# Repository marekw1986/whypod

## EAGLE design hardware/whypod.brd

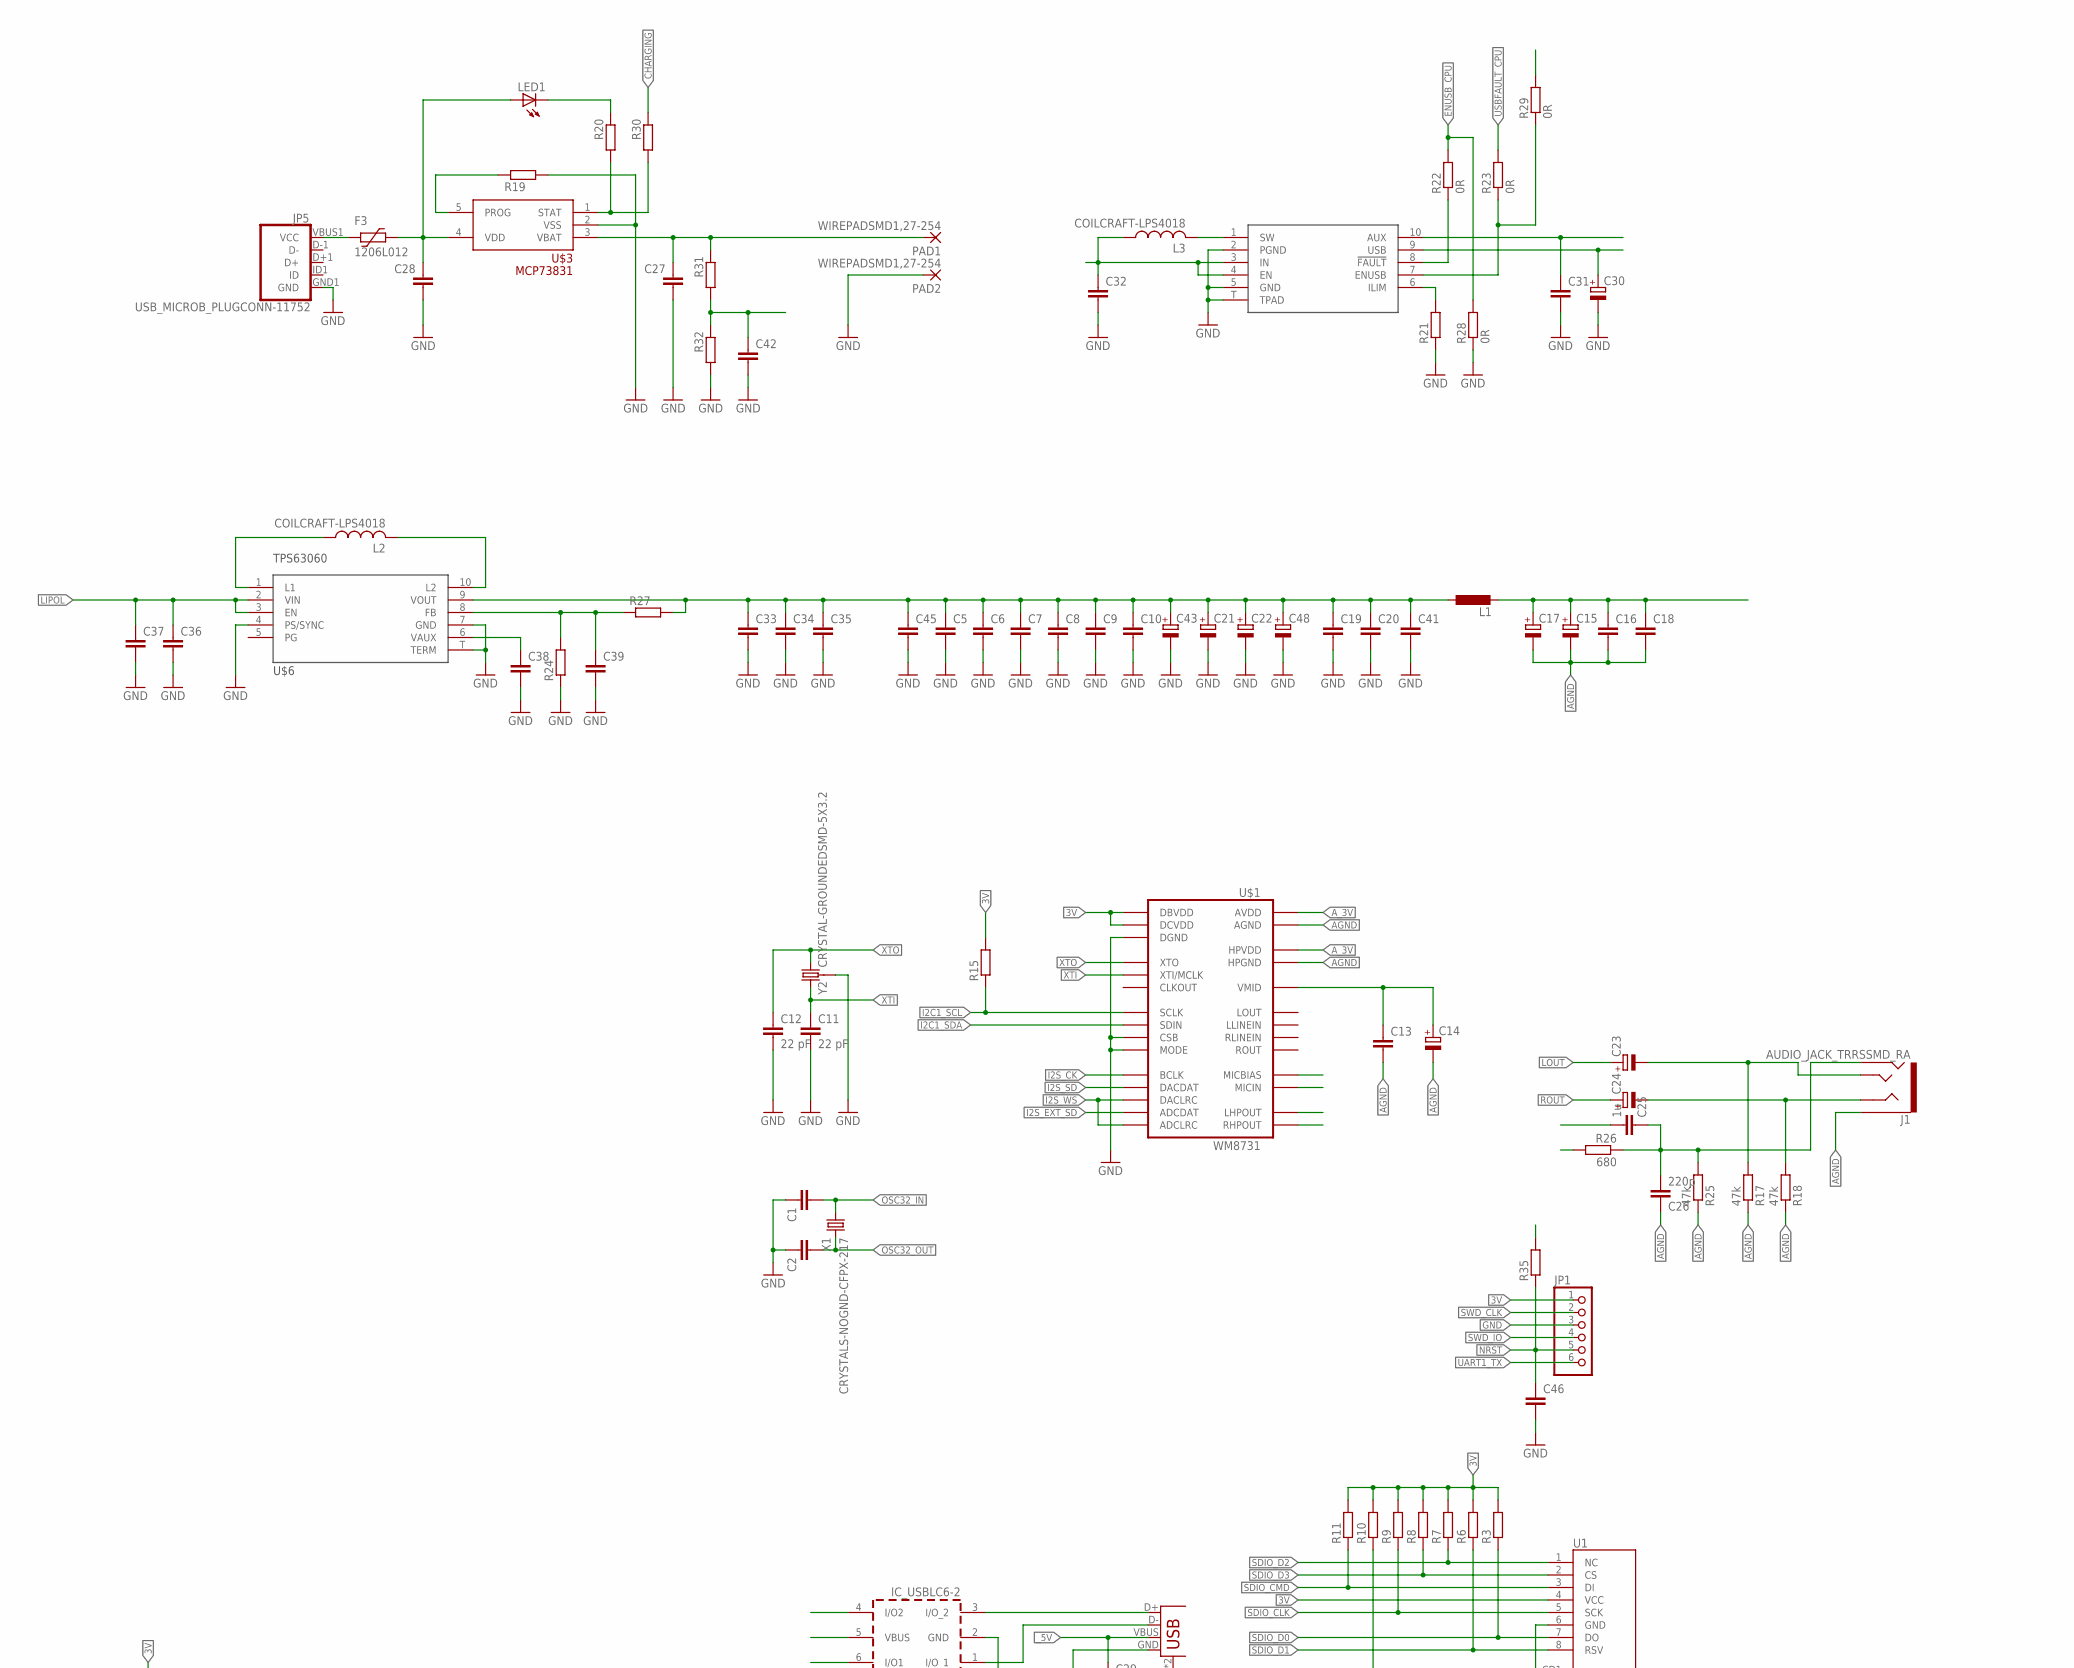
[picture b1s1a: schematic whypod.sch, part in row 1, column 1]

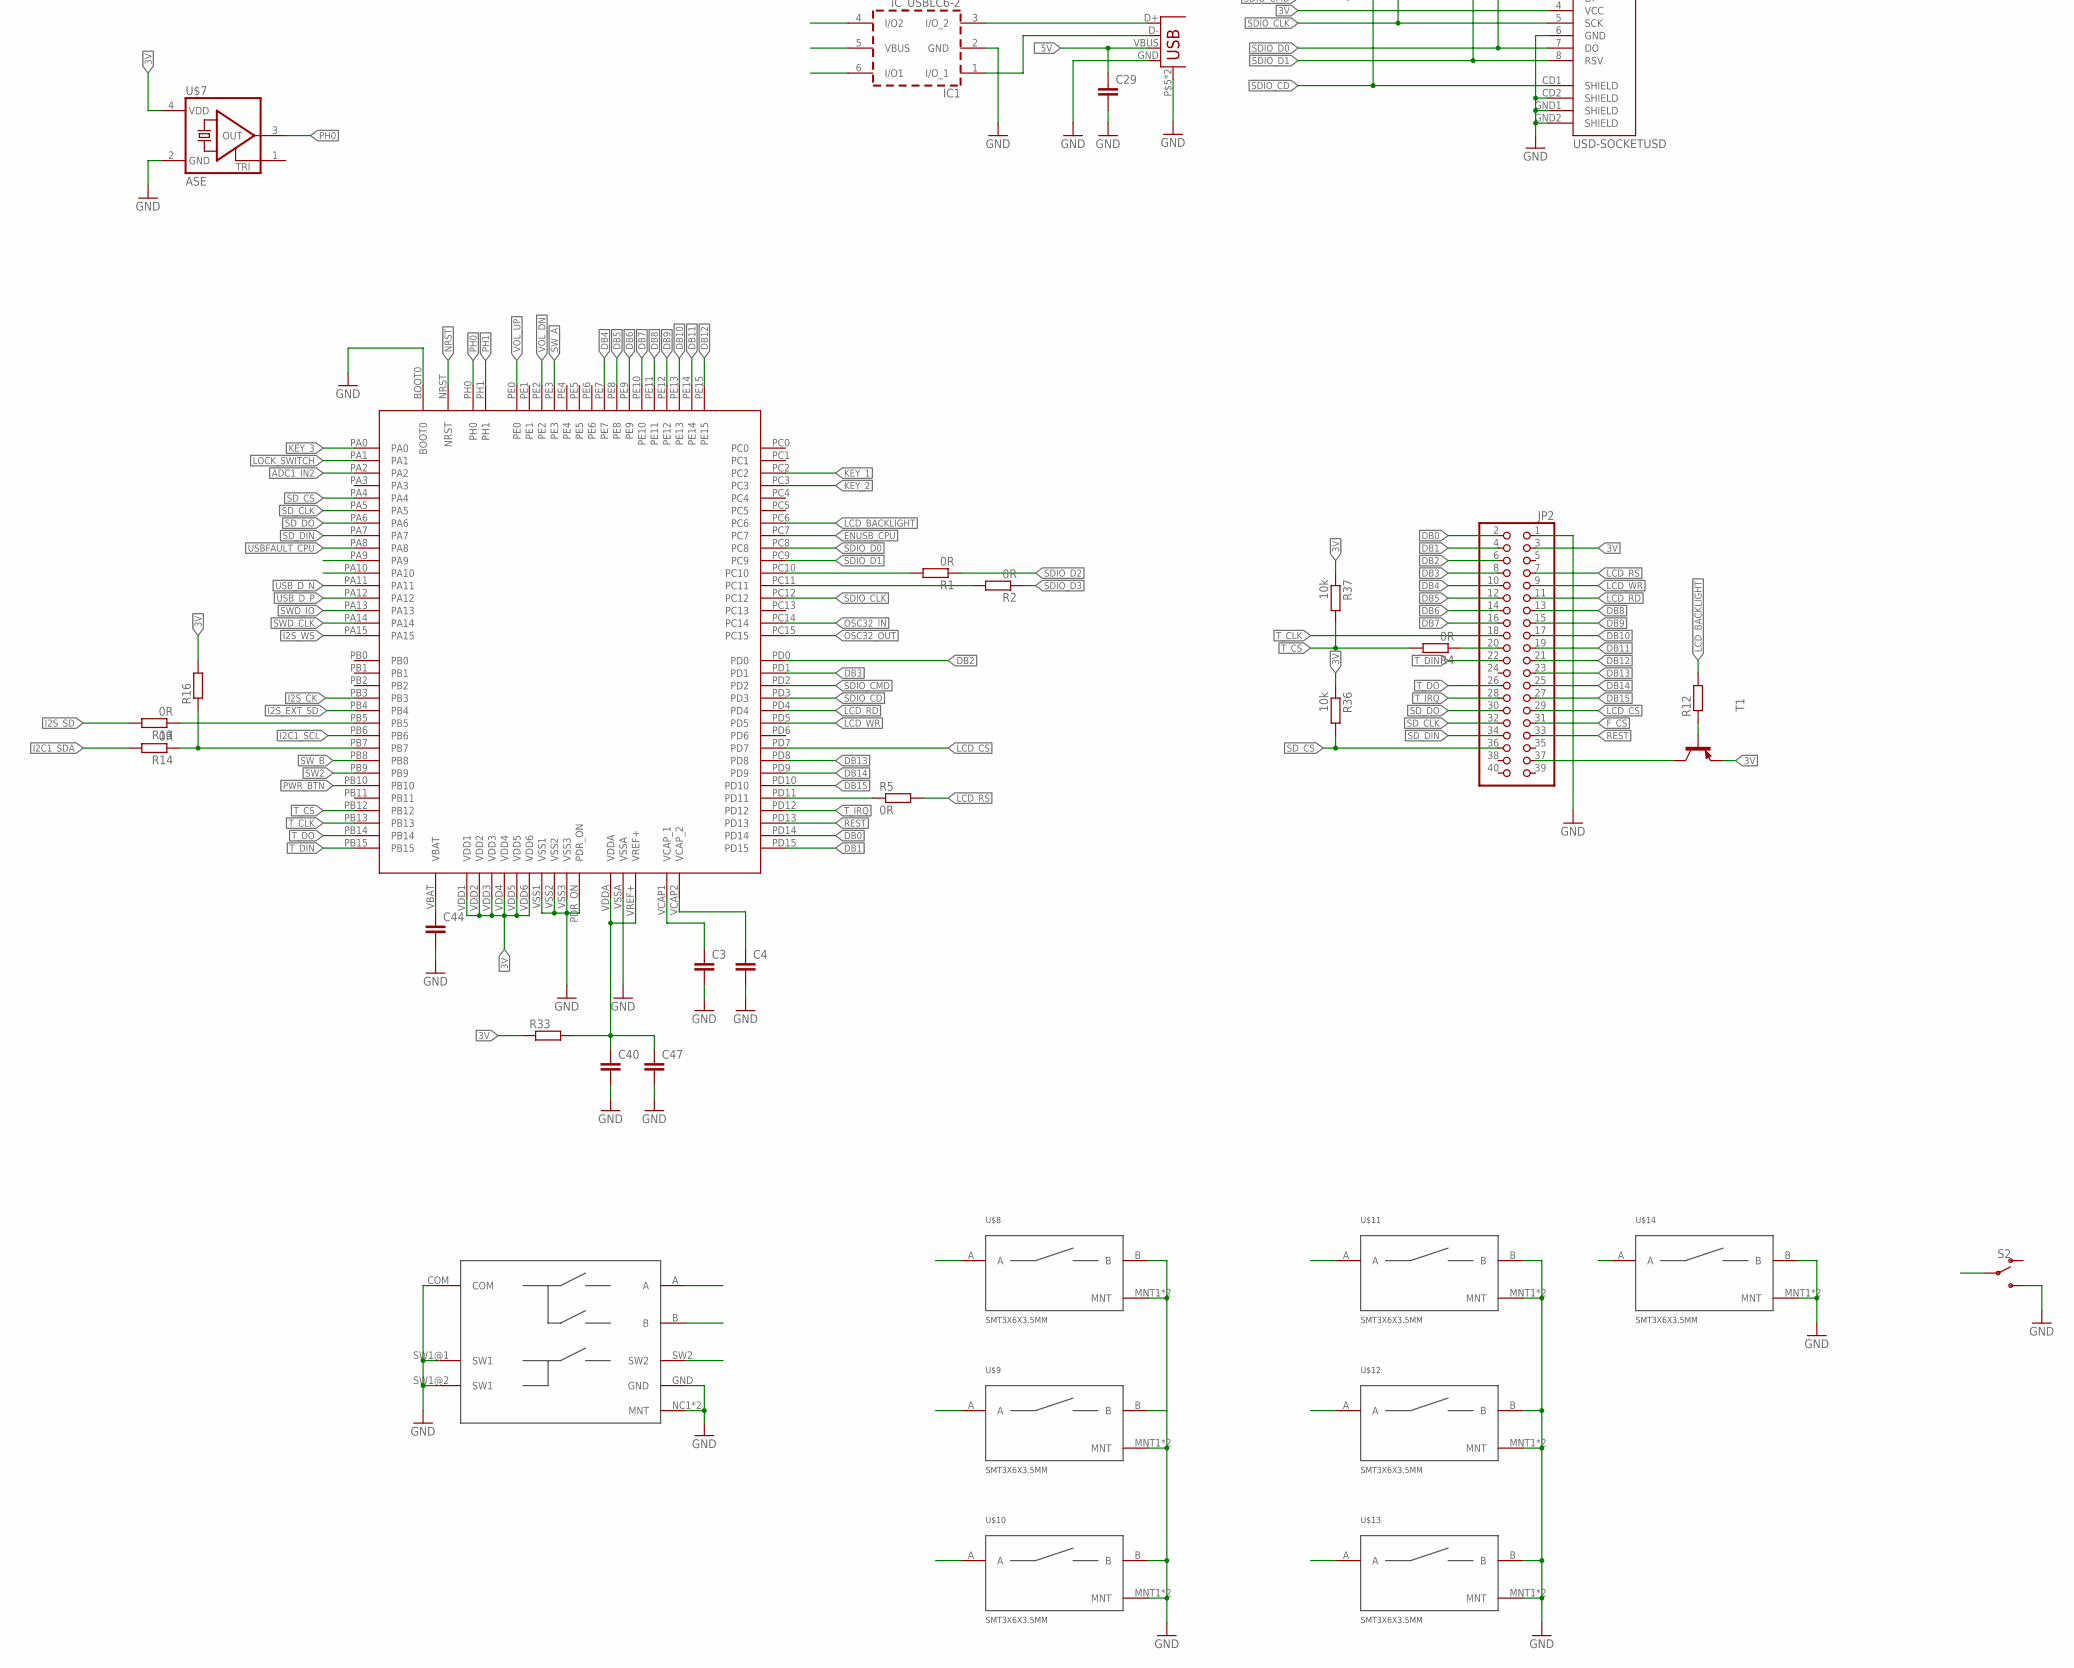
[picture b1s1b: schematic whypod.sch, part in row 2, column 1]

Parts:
C1, C2, C3, C4, C5, C6, C8, C9, C10, C13, C16, C18, C19, C20, C27, C28, C29, C31, C32, C38, C42, C46, C47: C-EUC0603; C0603
C7, C39, C40, C41, C44, C45: C-EUC0402; C0402
C11, C12: 22 pF; C0603
C14, C15, C17, C21, C22, C43, C48: CPOL-EUSMCA; SMC_A
C23, C24: CPOL-EUSMCE; SMC_E
C25: 1u; C0603
C26: 220p; C0603
C30: CPOL-EUSMCD; SMC_D
C33, C34, C35, C36, C37: C-EUC0805; C0805
F3: 1206L012; 1206L
IC1: IC_USBLC6-2; SOT-23-6L
J1: AUDIO_JACK_TRRSSMD_RA; AUDIO_JACK_3.5MM_TRRS_SMD_RA
JP1: PINHD-1X06_2.54-SMD-90°; 1X06SMD/90
JP2: PINHD-2X20_2.54-SMD; 2X20SMD
JP5: USB_MICROB_PLUGCONN-11752; USB-B-MICRO-SMD_V03
L1: L-EUL3225M; L3225M
L2, L3: COILCRAFT-LPS4018; LPS4018
LED1: LEDCHIP-LED0603; CHIP-LED0603
PAD1, PAD2: WIREPADSMD1,27-254; SMD1,27-2,54
R1, R2, R4, R5, R13, R14, R22, R23, R28, R29: 0R; R0603
R3, R6, R8, R10, R11, R15, R19, R20, R21, R30, R31, R32, R35: R-EU_R0603; R0603
R7, R9, R12, R16, R24, R27: R-EU_R0402; R0402
R17, R18, R25: 47k; R0603
R26: 680; R0603
R33: R-EU_M0805; M0805
R36, R37: 10k; R0603
S2: SWITCH-SPDT-SMD-RIGHT-ANGLE; SWITCH_SPST_SMD_A
T1: BC857A-PNP-SOT23-BEC; SOT23-BEC
U1: USD-SOCKETUSD; USD-SOCKET-PP
U$1: WM8731; 28-SSOP
U$2: STM32F4V_100PIN_GENERIC; LQFP100
U$3: MCP73831SOT-23-5; SOT-23-5
U$4: EVQWKSMD; EVQWK_SMD
U$5: TPS2500; DRC10
U$6: TPS63060; DRC10
U$7: ASE
U$8, U$9, U$10, U$11, U$12, U$13, U$14: SMT3X6X3.5MM
X1: CRYSTALS-NOGND-CFPX-217; 3.2X1.5-2-PAD
X2: USB-A-S
Y2: CRYSTAL-GROUNDEDSMD-5X3.2; CRYSTAL-SMD-5X3.2-4PAD

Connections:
3V: C5.1, C6.1, C7.1, C8.1, C9.1, C10.1, C19.1, C20.1, C21.+, C22.+, C33.1, C34.1, C35.1, C41.1, C43.+, C45.1, C48.+, JP1.1, JP2.3, L1.1, R3.2, R6.2, R7.2, R8.2, R9.2, R10.2, R11.2, R15.2, R16.2, R27.2, R29.2, R33.1, R35.2, R36.1, R37.1, T1.E, U1.4 (VCC), U$1.P$1 (DBVDD), U$1.P$27 (DCVDD), U$2.VDD1, U$2.VDD2, U$2.VDD3, U$2.VDD4, U$2.VDD5, U$2.VDD6, U$6.9 (VOUT), U$7.4 (VDD)
ADC1_IN2: C42.1, R31.2, R32.1, U$2.PA2
AGND: C13.2, C14.-, C15.-, C16.2, C17.-, C18.2, C26.1, J1.EARTH, R17.1, R18.1, R25.1, U$1.P$11 (HPGND), U$1.P$15 (AGND)
A_3V: C15.+, C16.1, C17.+, C18.1, L1.2, U$1.P$8 (HPVDD), U$1.P$14 (AVDD)
CHARGING: R30.1, U$2.PA10
DB0: JP2.2, U$2.PD14
DB1: JP2.4, U$2.PD15
DB2: JP2.6, U$2.PD0
DB3: JP2.8, U$2.PD1
DB4: JP2.10, U$2.PE7
DB5: JP2.12, U$2.PE8
DB6: JP2.14, U$2.PE9
DB7: JP2.16, U$2.PE10
DB8: JP2.13, U$2.PE11
DB9: JP2.15, U$2.PE12
DB10: JP2.17, U$2.PE13
DB11: JP2.19, U$2.PE14
DB12: JP2.21, U$2.PE15
DB13: JP2.23, U$2.PD8
DB14: JP2.25, U$2.PD9
DB15: JP2.27, U$2.PD10
ENUSB: R22.1, U$5.8 (!FAULT)
ENUSB_CPU: R22.2, R28.2, U$2.PC7
F_CS: JP2.31
GND: C1.1, C2.1, C3.2, C4.2, C5.2, C6.2, C7.2, C8.2, C9.2, C10.2, C11.2, C12.2, C19.2, C20.2, C21.-, C22.-, C27.2, C28.2, C29.2, C30.-, C31.2, C32.2, C33.2, C34.2, C35.2, C36.2, C37.2, C38.2, C39.2, C40.2, C41.2, C42.2, C43.-, C44.2, C45.2, C46.2, C47.2, C48.-, IC1.2 (GND), JP1.3, JP2.1, JP5.GND1 (GND), PAD2.1, R19.2, R21.1, R24.1, R28.1, R32.2, S2.3 (S), U1.6 (GND), U1.CD2 (SHIELD), U1.GND1 (SHIELD), U1.GND2 (SHIELD), U$1.P$21 (MODE), U$1.P$22 (CSB), U$1.P$28 (DGND), U$2.BOOT0, U$2.PDR_ON, U$2.VSS1, U$2.VSS2, U$2.VSS3, U$2.VSSA, U$3.2 (VSS), U$4.COM, U$4.GND, U$4.NC1 (MNT), U$4.NC2 (MNT), U$4.SW1@1 (SW1), U$4.SW1@2 (SW1), U$5.2 (PGND), U$5.5 (GND), U$5.T (TPAD), U$6.4 (PS/SYNC), U$6.7 (GND), U$6.T (TERM), U$7.2 (GND), U$8.B, U$8.MNT1 (MNT), U$8.MNT2 (MNT), U$9.B, U$9.MNT1 (MNT), U$9.MNT2 (MNT), U$10.B, U$10.MNT1 (MNT), U$10.MNT2 (MNT), U$11.B, U$11.MNT1 (MNT), U$11.MNT2 (MNT), U$12.B, U$12.MNT1 (MNT), U$12.MNT2 (MNT), U$13.B, U$13.MNT1 (MNT), U$13.MNT2 (MNT), U$14.B, U$14.MNT1 (MNT), U$14.MNT2 (MNT), X2.GND, X2.P$5 (SHIELD), X2.P$6 (SHIELD), Y2.2 (3), Y2.4 (3)
I2C1_SCL: R15.1, U$1.P$24 (SCLK), U$2.PB6
I2C1_SDA: R14.2, U$1.P$23 (SDIN)
I2S_CK: U$1.P$3 (BCLK), U$2.PB3
I2S_EXT_SD: U$1.P$6 (ADCDAT), U$2.PB4
I2S_SD: R13.2, U$1.P$4 (DACDAT)
I2S_WS: U$1.P$5 (DACLRC), U$1.P$7 (ADCLRC), U$2.PA15
KEY_1: U$2.PC2, U$11.A
KEY_2: U$2.PC3, U$12.A
KEY_3: U$2.PA0, U$13.A
LCD_BACKLIGHT: R12.2, U$2.PC6
LCD_CS: JP2.29, U$2.PD7
LCD_RD: JP2.11, U$2.PD4
LCD_RS: JP2.7, R5.2
LCD_WR: JP2.9, U$2.PD5
LED_A: JP2.37, T1.C
LIPOL: C27.1, C32.1, C36.1, C37.1, L3.1, PAD1.1, R31.1, U$3.3 (VBAT), U$5.3 (IN), U$5.4 (EN), U$6.2 (VIN), U$6.3 (EN)
LOCK_SWITCH: S2.2, U$2.PA1
LOUT: C23.+, U$1.P$9 (LHPOUT)
MICBIAS: R26.2, U$1.P$17 (MICBIAS)
MICIN: C25.2, U$1.P$18 (MICIN)
unnamed: IC1.3 (I/O_2), X2.D+
unnamed: IC1.1 (I/O_1), X2.D-
unnamed: JP2.20, R4.1
unnamed: R5.1, U$2.PD11
unnamed: R1.2, U$2.PC10
unnamed: C3.1, U$2.VCAP1 (VCAP_1)
unnamed: C4.1, U$2.VCAP2 (VCAP_2)
unnamed: R2.2, U$2.PC11
unnamed: R12.1, T1.B
unnamed: C13.1, C14.+, U$1.P$16 (VMID)
unnamed: C23.-, J1.TIP, R17.2
unnamed: R13.1, U$2.PB5
unnamed: C24.-, J1.RING1, R18.2
unnamed: R14.1, R16.1, U$2.PB7
unnamed: R19.1, U$3.5 (PROG)
unnamed: R20.2, R30.2, U$3.1 (STAT)
unnamed: LED1.C, R20.1
unnamed: F3.2, JP5.VBUS1 (VCC)
unnamed: R21.2, U$5.6 (ILIM)
unnamed: C31.1, U$5.10 (AUX)
unnamed: C38.1, U$6.6 (VAUX)
unnamed: L3.2, U$5.1 (SW)
unnamed: C39.1, R24.2, R27.1, U$6.8 (FB)
unnamed: L2.2, U$6.10 (L2)
unnamed: L2.1, U$6.1 (L1)
unnamed: C40.1, C47.1, R33.2, U$2.VDDA, U$2.VREF+
unnamed: C44.1, U$2.VBAT
unnamed: C25.1, C26.2, J1.RING2, R25.2, R26.1
NRST: C46.1, JP1.5, R35.1, U$2.NRST, U$14.A
OSC32_IN: C1.2, U$2.PC14, X1.1
OSC32_OUT: C2.2, U$2.PC15, X1.2
PH0: U$2.PH0, U$7.3 (OUT)
PH1: U$2.PH1
PWR_BTN: U$2.PB10, U$8.A
REST: JP2.33, U$2.PD13
ROUT: C24.+, U$1.P$10 (RHPOUT)
SDIO_CD: R10.1, U1.CD1 (SHIELD), U$2.PD3
SDIO_CLK: R9.1, U1.5 (SCK), U$2.PC12
SDIO_CMD: R11.1, U1.3 (DI), U$2.PD2
SDIO_D0: R3.1, U1.7 (DO), U$2.PC8
SDIO_D1: R6.1, U1.8 (RSV), U$2.PC9
SDIO_D2: R1.1, R7.1, U1.1 (NC)
SDIO_D3: R2.1, R8.1, U1.2 (CS)
SD_CLK: JP2.32, U$2.PA5
SD_CS: JP2.36, R36.2, U$2.PA4
SD_DIN: JP2.34, U$2.PA7
SD_DO: JP2.30, U$2.PA6
SW2: U$2.PB9, U$4.SW2
SWD_CLK: JP1.2, U$2.PA14
SWD_IO: JP1.4, U$2.PA13
SW_A: U$2.PE3, U$4.A
SW_B: U$2.PB8, U$4.B
T_CLK: JP2.18, U$2.PB13
T_CS: R4.2, R37.2, U$2.PB12
T_DIN: JP2.22, U$2.PB15
T_DO: JP2.26, U$2.PB14
T_IRQ: JP2.28, U$2.PD12
UART1_TX: JP1.6, U$2.PA9
USBFAULT: R23.1, R29.1, U$5.7 (ENUSB)
USBFAULT_CPU: R23.2, U$2.PA8
USB_D_N: IC1.6 (I/O1), U$2.PA11
USB_D_P: IC1.4 (I/O2), U$2.PA12
VBUS: C28.1, F3.1, LED1.A, U$3.4 (VDD)
VOL_DN: U$2.PE2, U$10.A
VOL_UP: U$2.PE0, U$9.A
XTI: C11.1, U$1.P$25 (XTI/MCLK), Y2.3 (1)
XTO: C12.1, U$1.P$26 (XTO), Y2.1 (2)
_5V: C29.1, C30.+, IC1.5 (VBUS), U$5.9 (USB), X2.VBUS

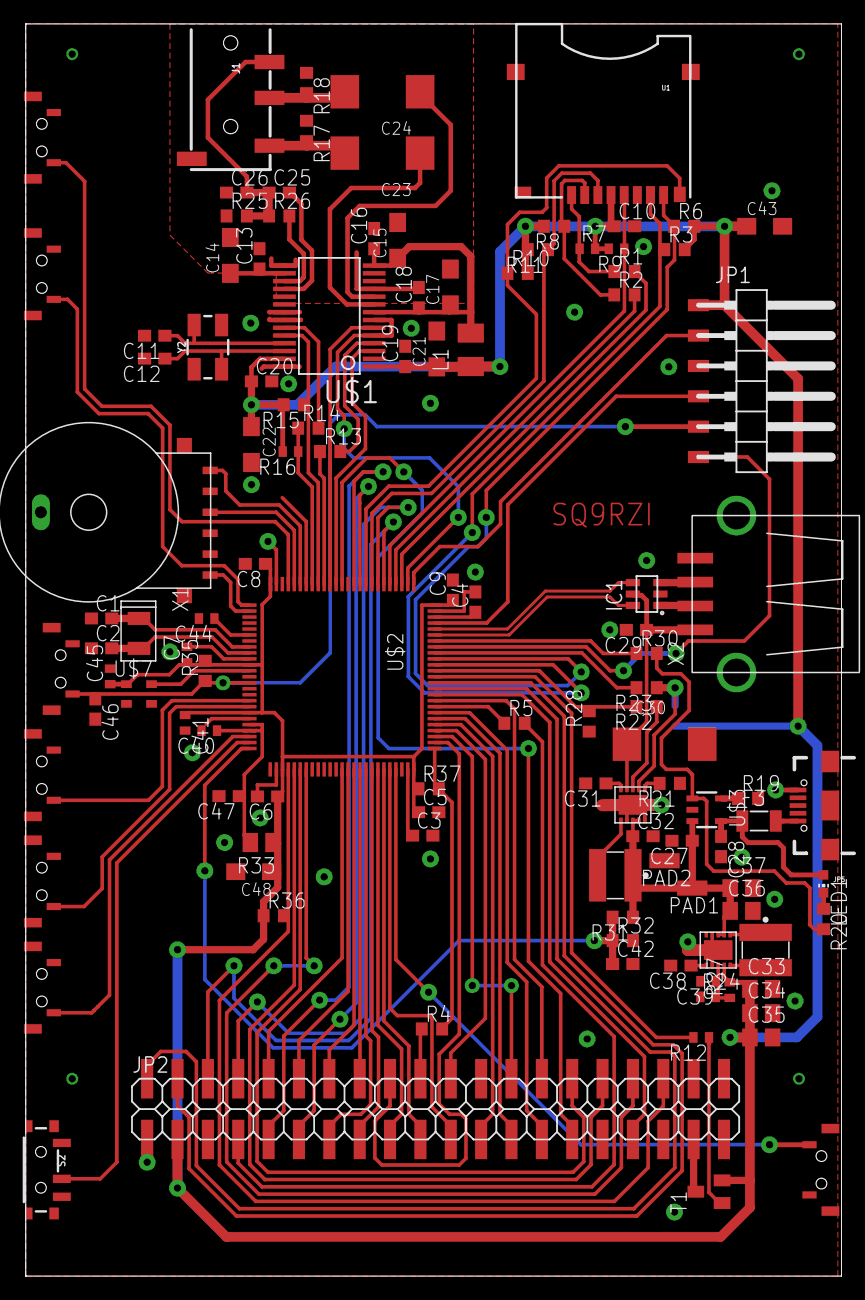
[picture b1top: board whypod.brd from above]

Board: 2 copper layers, 68.2 x 104.8 mm, 116 parts (1 on the bottom side), 111 nets.

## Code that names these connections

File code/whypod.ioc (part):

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PD7.Mode=NorPsramChipSelect1_1
PC7.GPIOParameters=GPIO_Label
PH0-OSC_IN.Signal=RCC_OSC_IN
PB10.GPIO_PuPd=GPIO_PULLUP
PA10.GPIO_PuPd=GPIO_PULLUP
PC12.Signal=SDIO_CK
PD3.GPIOParameters=GPIO_Label
PC6.GPIO_Label=LCD_BACKLIGHT
PB13.Signal=SPI2_SCK
RCC.SYSCLKSource=RCC_SYSCLKSOURCE_PLLCLK
PA9.GPIO_ModeDefaultOD=GPIO_MODE_AF_PP
PD4.Signal=FSMC_NOE
PB6.Signal=I2C1_SCL
PC7.Signal=GPIO_Output
PB6.Mode=I2C
PC3.Signal=GPIO_Input
PD0.Signal=FSMC_D2
PD8.Signal=FSMC_D13
PA1.GPIO_PuPd=GPIO_PULLUP
PB3.Mode=Full_Duplex_Master
PB12.GPIO_Label=T_IRQ
PE0.GPIOParameters=GPIO_PuPd,GPIO_Label
PA1.GPIOParameters=GPIO_PuPd,GPIO_Label
PE9.Signal=FSMC_D6
PB14.Mode=Full_Duplex_Master
PC9.Mode=SD_4_bits_Wide_bus
PE2.Signal=GPIO_Input
PA8.Signal=GPIO_Input
PE13.Mode=16b-d1
PE10.Signal=FSMC_D7
PD15.Mode=16b-d1
Mcu.Package=LQFP100
PB9.Signal=GPIO_Input
PA10.Signal=GPIO_Input
PB9.GPIO_PuPd=GPIO_PULLUP
PE9.Mode=16b-d1
PC11.Mode=SD_4_bits_Wide_bus
PD4.Mode=Lcd1
PB13.Mode=Full_Duplex_Master
PB10.GPIOParameters=GPIO_PuPd,GPIO_Label
PA4.GPIO_Label=SD_CS
PD15.Signal=FSMC_D1
PA5.Mode=Full_Duplex_Master
PE12.Mode=16b-d1
PD3.Signal=GPIO_Input
PB8.GPIO_PuPd=GPIO_PULLUP
PC6.Signal=GPIO_Output
PE10.Mode=16b-d1
PC2.Signal=GPIO_Input
PD13.GPIOParameters=GPIO_Label
PD7.Signal=FSMC_NE1
PD1.Signal=FSMC_D3
PC14-OSC32_IN.Signal=RCC_OSC32_IN
PA0-WKUP.GPIO_Label=KEY_3
PA0-WKUP.Signal=GPIO_Input
PC3.GPIOParameters=GPIO_PuPd,GPIO_Label
PE8.Mode=16b-d1
PD10.Signal=FSMC_D15
PB8.GPIO_Label=SW_B
PA8.GPIO_Label=USB_FAULT
PA9.Signal=USART1_TX
PD8.Mode=16b-d1
PB10.Signal=GPIO_Input
PB14.Signal=SPI2_MISO
PE2.GPIO_PuPd=GPIO_PULLUP
PA5.Signal=SPI1_SCK
PC12.Mode=SD_4_bits_Wide_bus
PD1.Mode=16b-d1
PE14.Signal=FSMC_D11
PE15.Signal=FSMC_D12
PE8.Signal=FSMC_D5
PC2.GPIOParameters=GPIO_PuPd,GPIO_Label
PA1.GPIO_Label=LOCK_SWITCH
PE3.GPIO_PuPd=GPIO_PULLUP
PA13.Mode=Serial_Wire
PC7.GPIO_Label=ENUSB
PC8.Mode=SD_4_bits_Wide_bus
PA4.Signal=GPIO_Output
PB5.Signal=I2S3_SD
PD11.Signal=FSMC_A16
PA11.Signal=USB_OTG_FS_DM
PE3.Signal=GPXTI3
PC3.GPIO_Label=KEY_2
PA0-WKUP.GPIO_PuPd=GPIO_PULLUP
PD2.Signal=SDIO_CMD
PB12.GPIO_PuPd=GPIO_PULLUP
PB12.GPIOParameters=GPIO_PuPd,GPIO_Label
PE15.Mode=16b-d1
PA6.Mode=Full_Duplex_Master
Mcu.UserName=STM32F407VGTx
PC10.Signal=SDIO_D2
PA9.GPIOParameters=GPIO_PuPd,GPIO_ModeDefaultOD
PA11.Mode=Device_Only
PB15.Signal=SPI2_MOSI
PD9.Mode=16b-d1
PD13.Signal=GPIO_Output
PA12.Signal=USB_OTG_FS_DP
PE11.Mode=16b-d1
PD10.Mode=16b-d1
PA8.GPIOParameters=GPIO_Label
PH0-OSC_IN.Mode=HSE-External-Oscillator
PD5.Mode=Lcd1
PA0-WKUP.GPIOParameters=GPIO_PuPd,GPIO_Label
RCC.HSE_VALUE=25000000
PA15.Mode=Full_Duplex_Master
PA4.GPIO_Speed=GPIO_SPEED_FREQ_VERY_HIGH
PB4.Mode=Full_Duplex_Master
PE13.Signal=FSMC_D10
PC14-OSC32_IN.Mode=LSE-External-Oscillator
PA14.Mode=Serial_Wire
PD14.Mode=16b-d1
PB5.Mode=Full_Duplex_Master
PA10.GPIO_Label=CHARGING
PE3.GPIOParameters=GPIO_PuPd,GPIO_Label,GPIO_ModeDefaultEXTI
PB7.Signal=I2C1_SDA
PH1-OSC_OUT.Mode=HSE-External-Oscillator
PD13.GPIO_Label=LCD_RST
PA6.Signal=SPI1_MISO
PA15.Signal=I2S3_WS
PE0.GPIO_Label=VOL_UP
PD3.GPIO_Label=SDIO_CD
PE7.Signal=FSMC_D4
PE2.GPIO_Label=VOL_DN
PC2.GPIO_Label=KEY_1
PB4.Signal=I2S3_ext_SD
PE0.GPIO_PuPd=GPIO_PULLUP
PE3.GPIO_ModeDefaultEXTI=GPIO_MODE_IT_FALLING
PC15-OSC32_OUT.Mode=LSE-External-Oscillator
PB8.GPIOParameters=GPIO_PuPd,GPIO_Label
PA7.Mode=Full_Duplex_Master
PB9.GPIO_Label=ROT_PUSH
PC11.Signal=SDIO_D3
PC8.Signal=SDIO_D0
PC10.Mode=SD_4_bits_Wide_bus
PD9.Signal=FSMC_D14
PD5.Signal=FSMC_NWE
PA9.GPIO_PuPd=GPIO_PULLUP
PB9.GPIOParameters=GPIO_PuPd,GPIO_Label
PA13.Signal=SYS_JTMS-SWDIO
PA9.Mode=Half_duplex(single_wire_mode)
PB10.GPIO_Label=PWR_BTN
PE2.GPIOParameters=GPIO_PuPd,GPIO_Label
PE11.Signal=FSMC_D8
PC15-OSC32_OUT.Signal=RCC_OSC32_OUT
PA1.Signal=GPIO_Input
PD2.Mode=SD_4_bits_Wide_bus
board=custom
PB15.Mode=Full_Duplex_Master
PE14.Mode=16b-d1
PA10.GPIOParameters=GPIO_PuPd,GPIO_Label
PH1-OSC_OUT.Signal=RCC_OSC_OUT
PA4.GPIOParameters=GPIO_Speed,GPIO_Label
PC2.GPIO_PuPd=GPIO_PULLUP
Mcu.Name=STM32F407V(E-G)Tx
PE0.Signal=GPIO_Input
PD0.Mode=16b-d1
PE12.Signal=FSMC_D9
PA2.Signal=ADCx_IN2
PD14.Signal=FSMC_D0
PB3.Signal=I2S3_CK
RCC.SYSCLKFreq_VALUE=168000000
PE7.Mode=16b-d1
PA12.Mode=Device_Only
PB7.Mode=I2C
PA14.Signal=SYS_JTCK-SWCLK
PD11.Mode=A16_1
PC6.GPIOParameters=GPIO_Label
PB8.Signal=GPIO_Input
PE3.GPIO_Label=SW_A
PC9.Signal=SDIO_D1
PB12.Signal=GPXTI12
PC3.GPIO_PuPd=GPIO_PULLUP
PA7.Signal=SPI1_MOSI

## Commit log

2020-11-22 minor changes
2020-11-23 Hardware updates
2020-11-24 Hardware updated
2020-11-26 PCB updates
2020-11-26 PCB updated
2020-11-27 DAC added
2020-11-28 Minor updates
2020-11-28 project updated
2020-12-02 USB power supply
2020-12-03 Power circuit updated
2020-12-16 Rotary encoder added
2020-12-18 Switches added
2020-12-19 32kHz oscillator added
2020-12-21 Some updates
2020-12-25 Some minor changes
2020-12-28 Some minor chnges
2021-04-09 Maior changes
2021-04-11 Minor change
2021-04-11 Some kind of joke. Generate again
2021-04-12 It is much better without RTOS!
2021-04-16 WM8731 codec
2023-09-05 New configuration

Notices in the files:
parts and their libraries:
SparkFun-Clocks: Licensing: Creative Commons ShareAlike 4.0 International - https://creativecommons.org/licenses/by-sa/4.0
